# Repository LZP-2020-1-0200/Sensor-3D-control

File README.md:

# Sensor-3D-control
Programmambe sensor stage

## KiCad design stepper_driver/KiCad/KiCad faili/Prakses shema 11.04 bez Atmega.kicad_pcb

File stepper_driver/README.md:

# Sensor-3D-control
Programmambe sensor stage

## Documentation
Documentation is auto-generated by doxygen.
Use `doxygen doxygen.cfg` to generate documentation.

## SCPI reference

### `*IDN?`

Prints identificator.

### `*RST`

Resets the state without restarting the entire module.

### `motor?`

prints all motor coordinates

Format: `<x> <y> <z>`

### `motor [X|Y|Z] `_`val`_

Sets the target coordinate to all motors or one motor specifically to _`val`_ switches state to 'targeting'

### `motor:lock?`

Prints out all motor lock states.

Format: `<1|0> <1|0> <1|0>`

Only prints `0` if that motor is completely unlocked, otherwise `1`

### `motor:lock [X|Y|Z] <ON|OFF>`

Locks/unlocks one or all motors.

Overrides any previous action that motors were doing. Both `ON` and `OFF` will stop the stepper(s) in their tracks

### `motor:state?`

Prints out the state of all motors.

Format: `<X.state> <Y.state> <Z.state>`

|State number|State name| Description |
|--|--|--|
|0|Disabled|The stepper is disabled (all magnets are off).|
|1|Idle|The stepper isn't moving, however some of the magnets are enabled and lock it in place.|
|2|Homing| The stepper is attempting to locate the start switch to reset it's internal coordinate system. Coordinate system resets only after the homing sequence is complete.|
|3|Targeting| The stepper is performing the targeting sequence.|

### `motor:state:default?`

Prints out the default state of all motors.

Format: `<default_state>`

States similar to `motor:state?` but prints out the default state instead of the current state.
State can be only 0 (Disabled) or 1 (Idle)

### `motor:state:default <0|1>`

Sets the default state of all motors.

State can be only 0 (Disabled) or 1 (Idle)

### `motor:end:<X|Y|Z>?`

prints out end switch status for specified axis.

Format: `<start> <end>`

`1` - switch triggered
`0` - switch not triggered

### `home`

Sets mode to 'homing' for all motors.

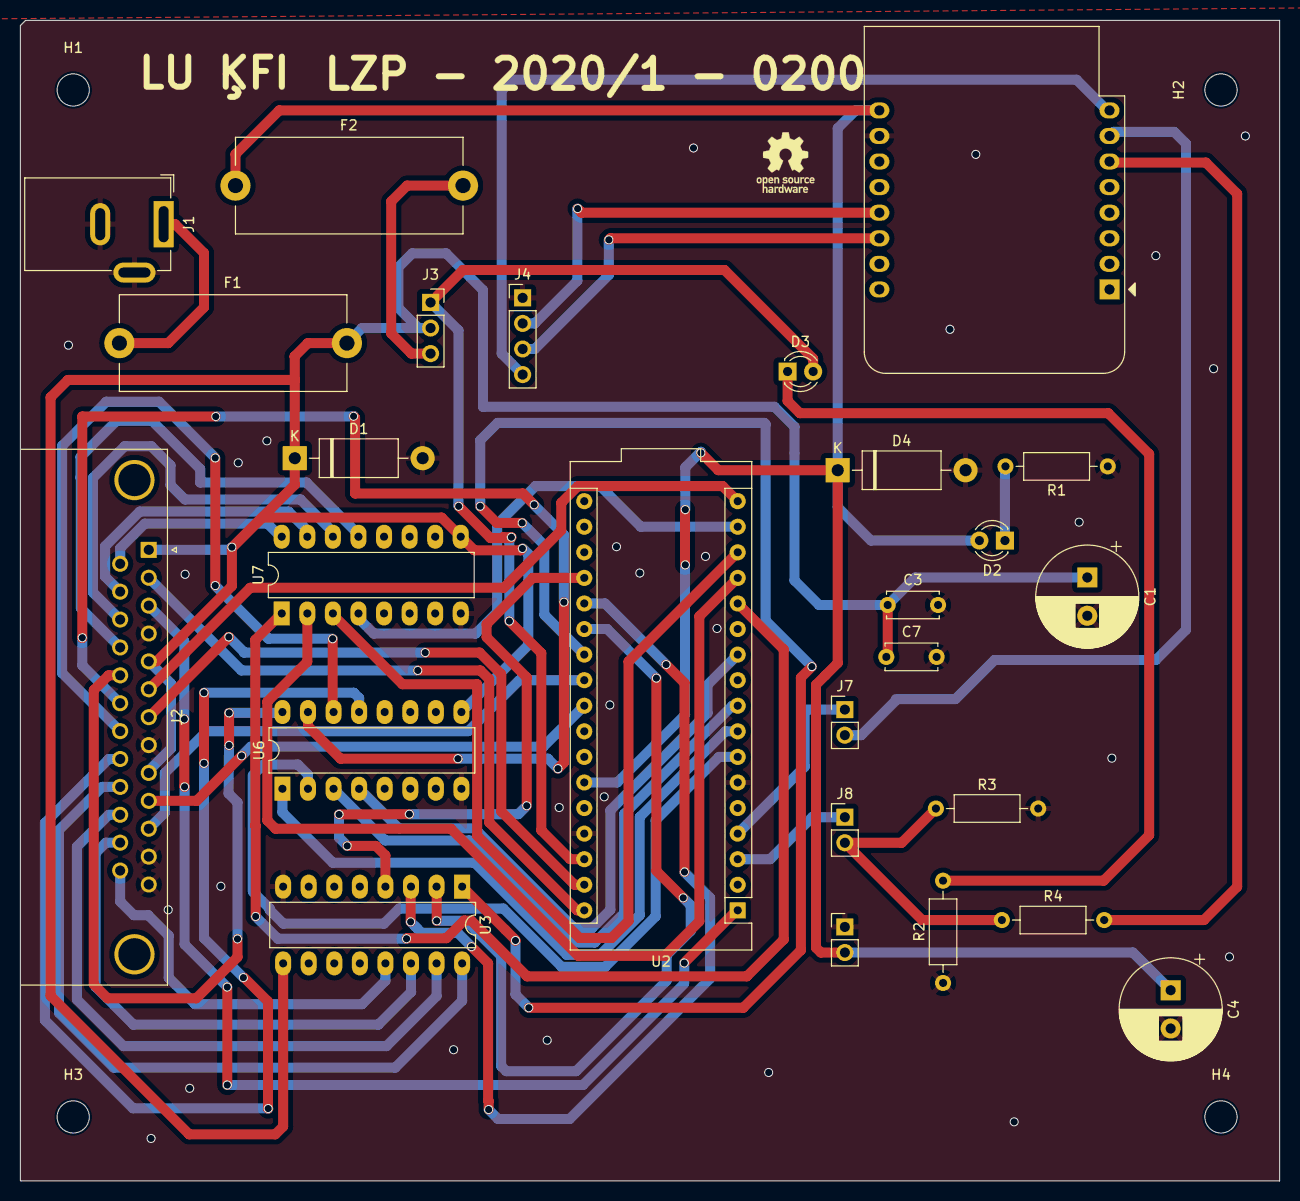
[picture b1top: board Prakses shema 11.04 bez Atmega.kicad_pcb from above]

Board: 2 copper layers, 125.1 x 115.3 mm, 30 parts (0 on the bottom side), 46 nets.

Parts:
C1, C4: 4,7uF; CP_Radial_D10.0mm_P3.80mm
C3: 68pF; C_Disc_D5.0mm_W2.5mm_P5.00mm
C7: 68 pF; C_Disc_D5.0mm_W2.5mm_P5.00mm
D1, D4: SA6.0A; D_DO-15_P12.70mm_Horizontal
D2, D3: LED; LED_D3.0mm
F1: 2A; Fuseholder_Cylinder-5x20mm_Stelvio-Kontek_PTF78_Horizontal_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
F2: 0,5A; Fuseholder_Cylinder-5x20mm_Stelvio-Kontek_PTF78_Horizontal_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
H1, H2, H3, H4: MountingHole; MountingHole_3.2mm_M3
J1: Barrel_Jack_Switch_Pin3; BarrelJack_GCT_DCJ200-10-A_Horizontal
J2: DB25_Plug; DSUB-25_Male_Horizontal_P2.77x2.84mm_EdgePinOffset9.90mm_Ho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
J3: Conn_01x03_Pin; PinSocket_1x03_P2.54mm_Vertical
J4: Conn_01x04_Pin; PinHeader_1x04_P2.54mm_Vertical
J6, J7, J8: Conn_01x02_Pin; PinHeader_1x02_P2.54mm_Vertical
R1, R2: 390; R_Axial_DIN0207_L6.3mm_D2.5mm_P10.16mm_Horizontal
R3, R4: 10k*; R_Axial_DIN0207_L6.3mm_D2.5mm_P10.16mm_Horizontal
U1: WeMos_D1_mini; WEMOS_D1_mini_light
U2: Arduino_Micro
U3, U6, U7: ULN2003; DIP-16_W7.62mm_LongPads

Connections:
+5V: C4.1, D2.2 (A), D4.1 (K), F2.1, J6.2, U1.9 (5V), U2.29 (+5V)
+7.5V: C1.1, C3.1, C7.1, D1.1 (K), F1.2, J2.1, J2.5, J2.9, J3.2, U3.9 (COM), U6.9 (COM), U7.9 (COM)
/D0/RX: J7.1, U2.4 (D0/RX)
/PB1: J2.2, U2.34 (D15)
/PB2: J2.3, U2.1 (D16)
/PB3: J2.7, U2.33 (D14)
/PB4: U2.13 (D8/A8), U7.1 (I1)
/PB5: U2.14 (~D9/A9), U7.2 (I2)
/PB6: U2.15 (~D10/A10), U7.3 (I3)
/PB7: U2.16 (~D11), U7.4 (I4)
/PD0: U2.8 (~D3/SCL), U6.1 (I1)
/PD1: U2.7 (D2/SDA), U6.2 (I2)
/PD3: J8.1, U2.3 (D1/TX)
/PD4: U2.9 (D4/A6), U6.3 (I3)
/PD6: J2.6, U2.17 (D12/A11)
/PD7: U2.11 (~D6/A7), U6.4 (I4)
/PF0: J2.10, U2.26 (A5/D23)
/PF1: J2.11, U2.25 (A4/D22)
/PF4: U2.24 (A3/D21), U3.1 (I1)
/PF5: U2.23 (A2/D20), U3.2 (I2)
/PF6: U2.22 (A1/D19), U3.3 (I3)
/PF7: U2.21 (A0/D18), U3.4 (I4)
/Vin_: F1.1, J1.1
GND: C1.2, C3.2, C4.2, C7.2, D1.2 (A), D4.2 (A), J1.2, J1.3, J2.4, J2.8, J2.12, J2.13, J4.1, J6.1, R1.1, R2.1, R3.2, U1.10 (GND), U2.6 (GND), U2.31 (GND), U3.8 (GND), U6.8 (GND), U7.8 (GND)
unnamed: D2.1 (K), R1.2
unnamed: D3.2 (A), J3.1, U2.32 (VIN)
unnamed: D3.1 (K), R2.2
unnamed: J2.14, U7.16 (O1)
unnamed: J2.15, U7.15 (O2)
unnamed: J2.16, U7.14 (O3)
unnamed: J2.17, U7.13 (O4)
unnamed: J2.18, U6.16 (O1)
unnamed: J2.19, U6.15 (O2)
unnamed: J2.20, U6.14 (O3)
unnamed: J2.21, U6.13 (O4)
unnamed: J2.22, U3.16 (O1)
unnamed: J2.23, U3.15 (O2)
unnamed: J2.24, U3.14 (O3)
unnamed: J2.25, U3.13 (O4)
unnamed: F2.2, J3.3
unnamed: J4.2, U1.13 (SDA/D2)
unnamed: J4.3, U1.14 (SCL/D1)
unnamed: J4.4, U1.8 (3V3)
unnamed: J7.2, U1.7 (CS/D8)
unnamed: J8.2, R3.1, R4.1
unnamed: R4.2, U1.6 (MOSI/D7)

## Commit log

2023-03-07 led active low
2023-03-07 timer3 strādā
2023-03-08 motors griežas
2023-03-14 Stepper class changes with command support
2023-03-14 Konektora apraksts
2023-06-07 Add files via upload
    Man šķiet, ka šis ir īstais
2023-06-26 project config changes
2023-06-26 reporter and vector classes added
2023-06-26 putty del char handling in scipi
2023-06-26 stepper class setup
2023-06-26 end switch class
2023-06-26 event clock class with 1ms timer set up
2023-06-26 stepper controller class added It manages multilayered state machines that influence a stepper and 2 end switches
2023-06-26 update to main to use the new classes
2023-08-22 carriage returns
2023-08-22 stepper controller refactor
2023-08-22 tests
2023-08-22 spaces
2023-08-22 scpi rework
2023-08-24 end switch reset
2023-08-24 stepper reset
2023-08-24 SERIAL was taken, swapped to SERIAL_NUMBER
2023-08-24 Stepper controller update
2023-08-24 copy constructor deletion and serial print
2023-08-24 SCPI refactor
2023-08-24 Add a CMD dump and init msg
2023-08-24 ON, OFF => 1, 0
2023-08-24 motor state default get set
2023-08-24 writing some readme info
2023-08-24 minor constant tweak
2023-08-28 v1.0.0
2023-08-28 v1.0.1-alpha.0
2023-08-28 moved files downwards
2023-09-05 wireless interface first commit
2023-09-08 fixed messages to respond passthrough routes take up less memory
2023-09-13 State machine refactor and doxygen autodoc
2023-09-13 test name update
2023-09-18 restructure for raw and help
2023-09-25 raw mode and help update
2023-09-25 platformio config change
2023-10-02 flipped y axis
2023-10-02 client interface changes and live logs
2023-10-02 extra motor command option
2023-10-02 dependency update
2023-10-02 removed old manual auth
